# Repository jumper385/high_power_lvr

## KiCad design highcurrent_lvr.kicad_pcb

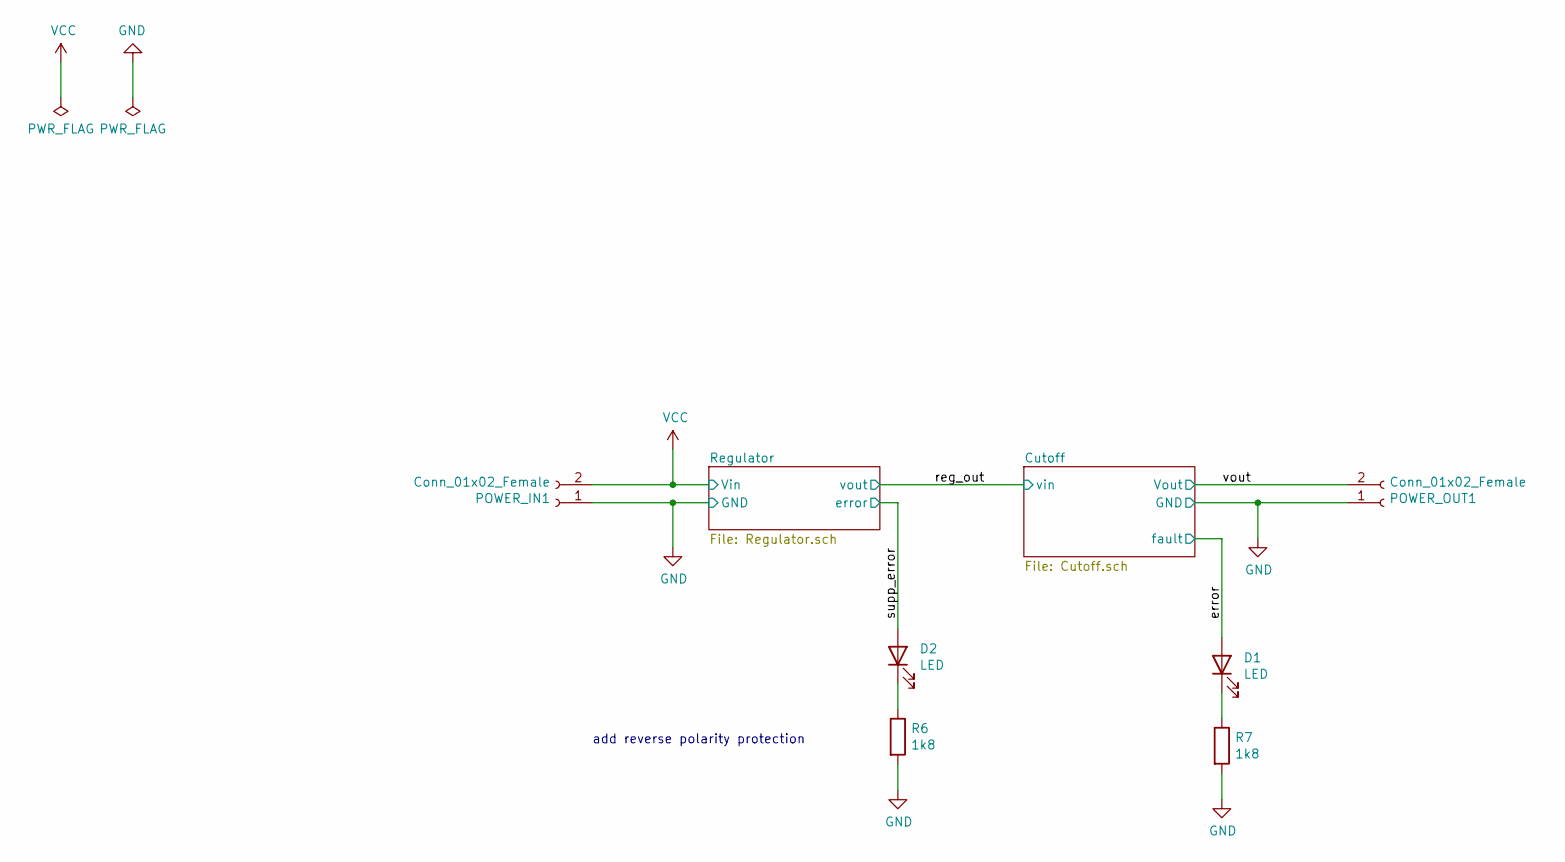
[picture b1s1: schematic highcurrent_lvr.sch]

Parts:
D1, D2: LED; LED_0805_2012Metric_Pad1.15x1.40mm_HandSolder
POWER_IN1: Conn_01x02_Female; connector-wire-3cm2-2pin-smd
POWER_OUT1: Conn_01x02_Female; connector-wire-3cm2-2pin-smd
R6, R7: 1k8; R_0805_2012Metric_Pad1.20x1.40mm_HandSolder

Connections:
/error: D1.2 (A); also elsewhere on the board
/supp_error: D2.2 (A); also elsewhere on the board
/vout: POWER_OUT1.2; also elsewhere on the board
GND: POWER_IN1.1, POWER_OUT1.1, R6.2, R7.2; also elsewhere on the board
unnamed: D1.1 (K), R7.1
unnamed: D2.1 (K), R6.1
VCC: POWER_IN1.2; also elsewhere on the board

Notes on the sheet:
add reverse polarity protection

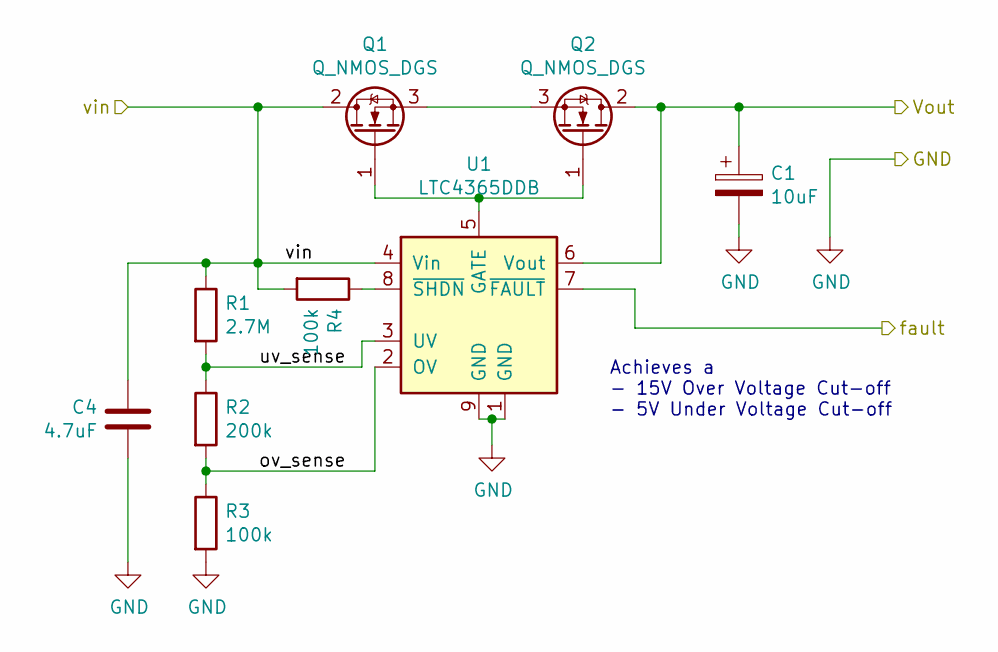
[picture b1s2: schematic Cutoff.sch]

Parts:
C1: 10uF; C_0805_2012Metric_Pad1.18x1.45mm_HandSolder
C4: 4.7uF; C_0805_2012Metric_Pad1.18x1.45mm_HandSolder
Q1, Q2: Q_NMOS_DGS; TO-252-2
R1: 2.7M; R_0805_2012Metric_Pad1.15x1.40mm_HandSolder
R2: 200k; R_0805_2012Metric_Pad1.15x1.40mm_HandSolder
R3, R4: 100k; R_0805_2012Metric_Pad1.15x1.40mm_HandSolder
U1: LTC4365DDB; DFN-8-1EP_2x3mm_P0.5mm_EP0.61x2.2mm

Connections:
/Cutoff/ov_sense: R2.2, R3.1, U1.2 (OV)
/Cutoff/uv_sense: R1.2, R2.1, U1.3 (UV)
/error: U1.7 (~FAULT); also elsewhere on the board
/reg_out: C4.2, Q1.2 (D), R1.1, R4.2, U1.4 (Vin); also elsewhere on the board
/vout: C1.1, Q2.2 (D), U1.6 (Vout); also elsewhere on the board
GND: C1.2, C4.1, R3.2, U1.1 (GND), U1.9 (GND); also elsewhere on the board
unnamed: Q1.1 (G), Q2.1 (G), U1.5 (GATE)
unnamed: Q1.3 (S), Q2.3 (S)
unnamed: R4.1, U1.8 (~SHDN)

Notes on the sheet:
Achieves a - 15V Over Voltage Cut-off - 5V Under Voltage Cut-off

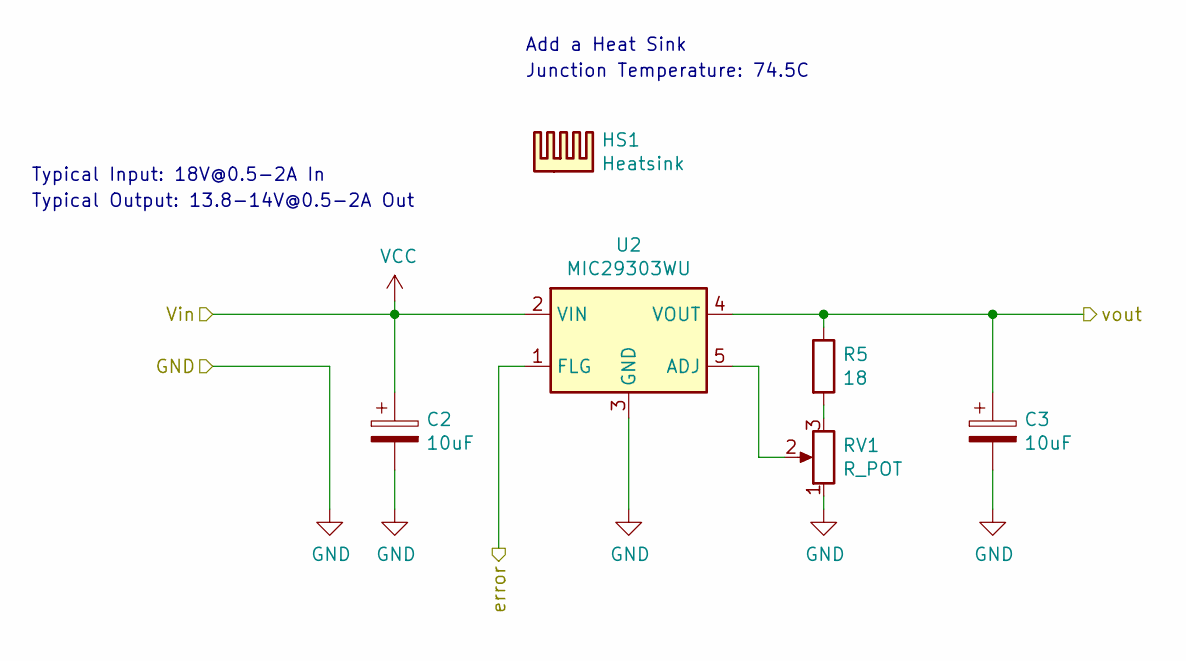
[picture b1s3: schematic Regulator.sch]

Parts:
C2, C3: 10uF; C_0805_2012Metric_Pad1.18x1.45mm_HandSolder
HS1: Heatsink; Ohmite-BGAH450125E
R5: 18; R_0805_2012Metric_Pad1.15x1.40mm_HandSolder
RV1: R_POT; TC33X-2-201G
U2: MIC29303WU; TO-263-5_TabPin3

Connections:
/reg_out: C3.1, R5.1, U2.4 (VOUT); also elsewhere on the board
/supp_error: U2.1 (FLG); also elsewhere on the board
GND: C2.2, C3.2, RV1.1, U2.3 (GND); also elsewhere on the board
unnamed: R5.2, RV1.3
unnamed: RV1.2, U2.5 (ADJ)
VCC: C2.1, U2.2 (VIN); also elsewhere on the board

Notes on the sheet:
Typical Input: 18V@0.5-2A In
Typical Output: 13.8-14V@0.5-2A Out
Add a Heat Sink
Junction Temperature: 74.5C

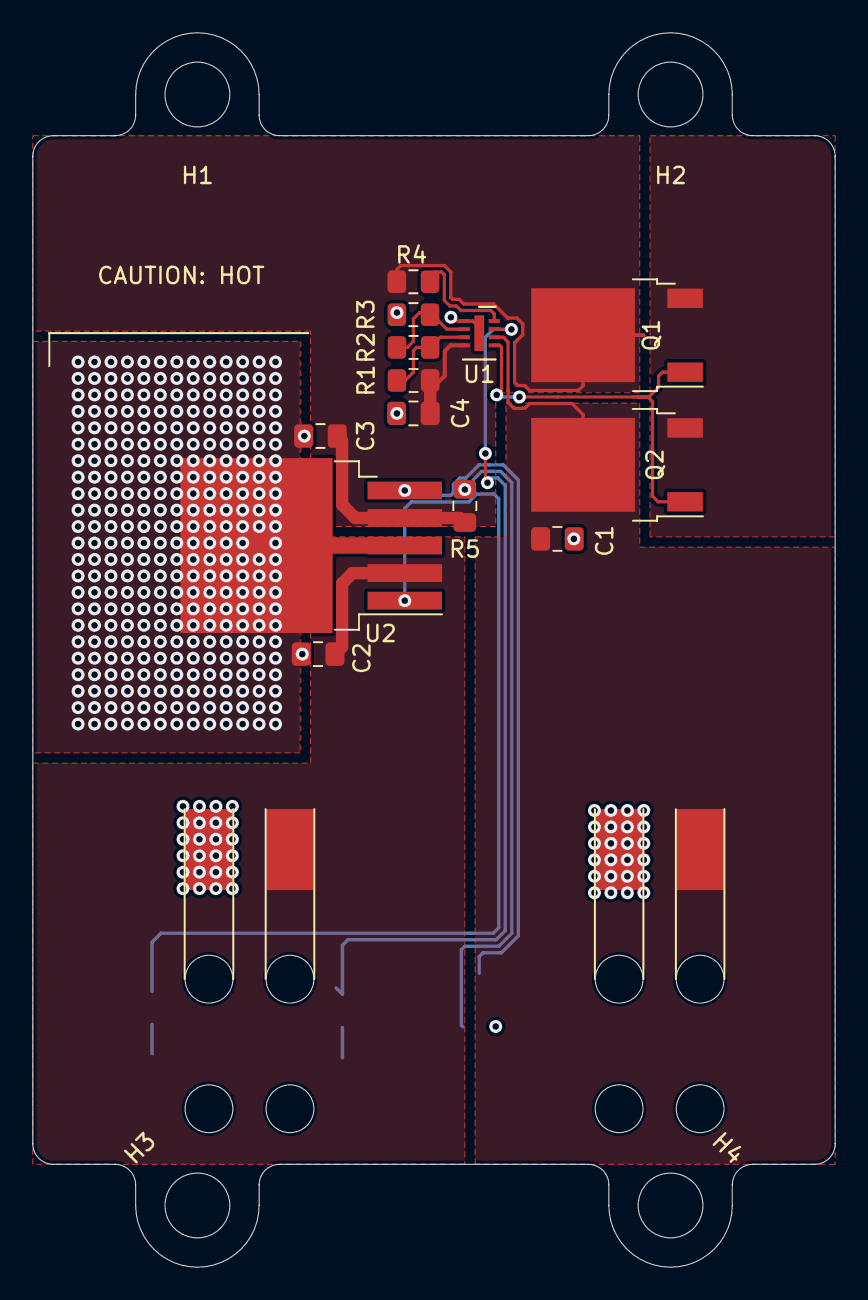
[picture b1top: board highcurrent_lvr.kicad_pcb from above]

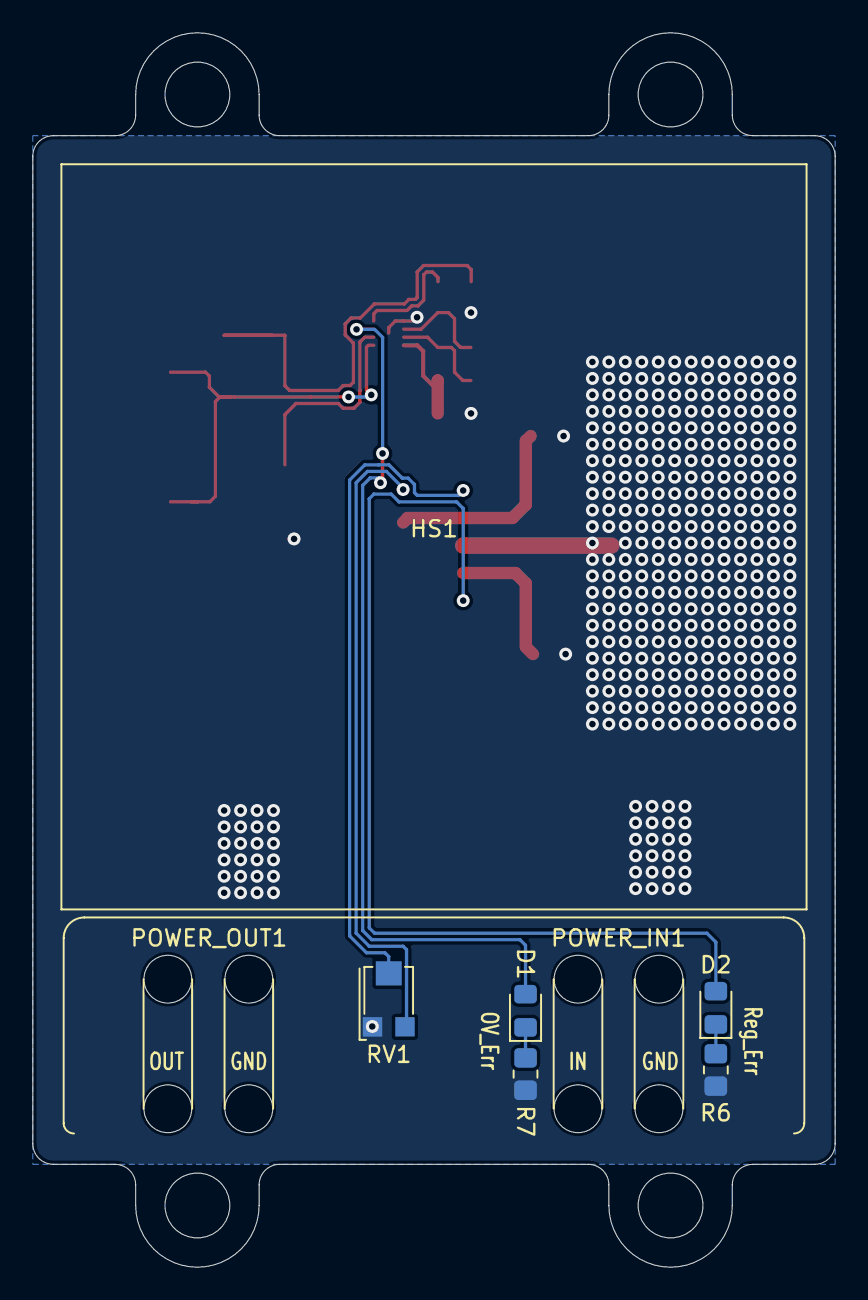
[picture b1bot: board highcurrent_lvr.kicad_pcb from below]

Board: 2 copper layers, 49.5 x 76.2 mm, 25 parts (6 on the bottom side), 15 nets.

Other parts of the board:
H1, H2, H3, H4: MountingHole; MountingHole_4mm

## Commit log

2021-02-21 fixed pcb layout
2021-02-27 added new heatsink alterantive
2021-02-27 changed layout for heat sink w/ issue #1
2021-02-28 added panelization
